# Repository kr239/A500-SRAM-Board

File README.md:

# A500-SRAM-Board

As with the previous DRAM board project, this will allow you to replace the old 44256 DRAM chips on your A500 with newer SRAM memory - a single 8Mbit chip, in fact. 

It's a lot simpler design, as there's just the single SRAM chip, a single 74ABT00 Quad NAND and a 74ABT821 10-bit D-Type Flip-Flop multiplexing the address lines.

The SRAM chip is a CY62157ESL-45ZSXI available from Mouser for less than £9 (at time of writing).

Ignore the image of the sockets, it's what KiCad generates as the 3D model.

Project is all done in KiCad 5.1.2

# Bill of Materials

4 x X7R 0.1uF MLCC SMD Capacitors (1206 (imperial)) - https://www.mouser.co.uk/ProductDetail/KEMET/C1206C104K4RACAUTO?qs=ds50AKTGxA8wfdh9NdUErA%3D%3D

1 x CY62157ESL-45ZSXI 8Mbit (512K x 16) SRAM (Cypress) - https://www.mouser.co.uk/ProductDetail/Cypress-Semiconductor/CY62157ESL-45ZSXI?qs=sGAEpiMZZMt9mBA6nIyysFkPZ0BxsYL2O8lsqoQk61s%3D

1 x SN74ABT821ADWR (SOIC-24) 10-bit D-Type Flip Flop (Texas Instruments) - https://www.mouser.co.uk/ProductDetail/Texas-Instruments/SN74ABT821ADWR?qs=FM6NhYOeeBXxX%2Fnpl0SzFQ%3D%3D

1 x 74ABT00D-T Quad Input NAND Gate (Nexperia) - https://www.mouser.co.uk/ProductDetail/Nexperia/74ABT00D118?qs=sGAEpiMZZMtMa9lbYwD6ZKUVY3zpSJbelxTPifZhJv0%3D

16 x 10-pin SIL Headers (Harwin M20-9991046) - https://www.mouser.co.uk/ProductDetail/Harwin/M20-9991046?qs=%2Fha2pyFaduidlkUepihCFfAt%252B%2FaLAftwmcRSbK8wUk3YgWpZFdsPYA%3D%3D

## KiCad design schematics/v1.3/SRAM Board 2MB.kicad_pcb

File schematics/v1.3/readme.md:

This is a significantly revised design based around two SRAM chips, using the buffered A9 input from U34 to provide sufficient address lines. This board will give 2MB CHIP RAM in an A500+ & the trapdoor expansion will be rendered useless for any memory expansions.

This board also has seen the design optimized significantly for low z-height, meaning it shouldn't foul the keyboard in a stock A500+ case. 

v1.3 also sees the introduction of an additional D-Type, Positive Edge triggered flip flop to feed A18 on the SRAM, rather than relying on /BRAS0 alone.

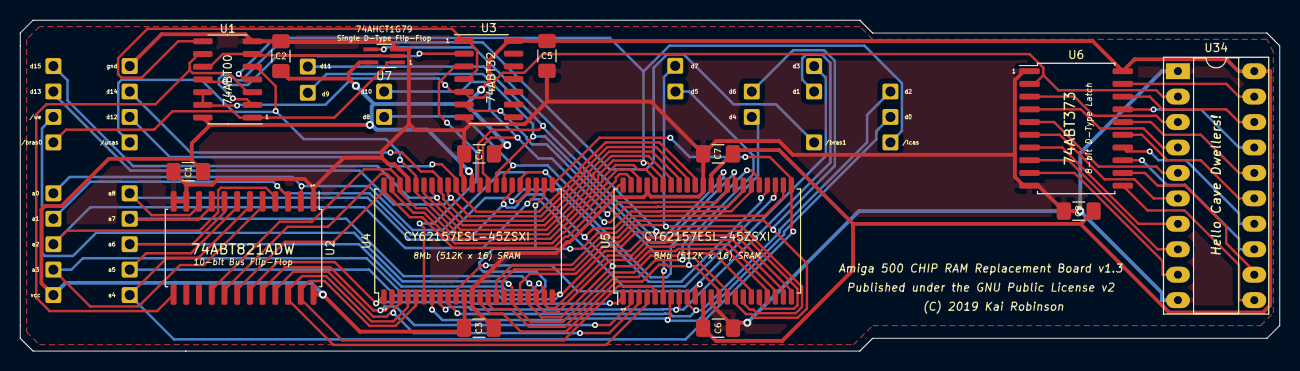
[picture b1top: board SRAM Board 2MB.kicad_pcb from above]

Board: 2 copper layers, 125.7 x 33.0 mm, 48 parts (0 on the bottom side), 64 nets.

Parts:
C1, C2, C3, C4, C5, C6, C7, C8: 0.1uF; C_1206_3216Metric_Pad1.42x1.75mm_HandSolder
J1, J2, J3, J4, J5, J6, J7, J8, J9, J10, J11, J12, J13, J14, J15, J16, J17, J18, J19, J20, J21, J22, J23, J24, J25, J26, J27, J28, J29, J30, J31, J32: Conn_01x01; PinHeader_1x01_P2.54mm_Vertical
U1: 74ABT00; SOIC-14_3.9x8.7mm_P1.27mm
U2: 74ABT821ADW; SOIC-24W_7.5x15.4mm_P1.27mm
U3: 74ABT32; SOIC-14_3.9x8.7mm_P1.27mm
U4, U5: CY62157ESL-45ZSXI; TSOP-II-44_10.16x18.41mm_P0.8mm_copy
U6: 74ABT373; SOIC-20W_7.5x12.8mm_P1.27mm
U7: 74AHCT1G79; SOT-353_SC-70-5_Handsoldering
U34: 74LS373; DIP-20_W7.62mm_Socket_LongPads

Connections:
/1d: U6.3, U34.3
/2d: U6.4, U34.4
/2q: U6.5, U34.5
/3d: U6.7, U34.7
/3q: U6.6, U34.6
/4d: U6.8, U34.8
/4q: U6.9, U34.9
/5d: U6.13, U34.13
/5q: U6.12, U34.12
/6d: U6.14, U34.14
/6q: U6.15, U34.15
/7d: U6.17, U34.17
/7q: U6.16, U34.16
/8d: U6.18, U34.18
/8q: U6.19, U34.19
/_bras0: J17.1, U1.1, U7.1
/_bras1: J18.1, U1.2
/_cas: U1.6, U1.10, U7.2
/_ceu4: U3.3, U4.6
/_ceu5: U3.6, U5.6
/_invbdra9: U1.11, U3.2
/_lcas: J22.1, U1.4, U4.39, U5.39
/_sramce: U1.8, U3.1, U3.4
/_ucas: J21.1, U1.5, U4.40, U5.40
/_we: J23.1, U4.17, U5.17
/a0: J24.1, U2.2, U4.27, U5.27
/a1: J25.1, U2.3, U4.26, U5.26
/a2: J26.1, U2.4, U4.25, U5.25
/a3: J27.1, U2.5, U4.24, U5.24
/a4: J28.1, U2.6, U4.23, U5.23
/a5: J29.1, U2.7, U4.22, U5.22
/a6: J30.1, U2.8, U4.21, U5.21
/a7: J31.1, U2.9, U4.20, U5.20
/a8: J32.1, U2.10, U4.19, U4.28, U5.19, U5.28
/a18: U4.18, U5.18, U7.4
/bdra9: U1.12, U1.13, U3.5, U6.2, U34.2
/clk: U1.3, U1.9, U2.13
/d0: J1.1, U4.7, U5.7
/d1: J2.1, U4.8, U5.8
/d2: J3.1, U4.9, U5.9
/d3: J4.1, U4.10, U5.10
/d4: J5.1, U4.13, U5.13
/d5: J6.1, U4.14, U5.14
/d6: J7.1, U4.15, U5.15
/d7: J8.1, U4.16, U5.16
/d8: J9.1, U4.29, U5.29
/d9: J10.1, U4.30, U5.30
/d10: J11.1, U4.31, U5.31
/d11: J12.1, U4.32, U5.32
/d12: J13.1, U4.35, U5.35
/d13: J14.1, U4.36, U5.36
/d14: J15.1, U4.37, U5.37
/d15: J16.1, U4.38, U5.38
/ma0: U2.23, U4.5, U5.5
/ma1: U2.22, U4.4, U5.4
/ma2: U2.21, U4.3, U5.3
/ma3: U2.20, U4.2, U5.2
/ma4: U2.19, U4.1, U5.1
/ma5: U2.18, U4.44, U5.44
/ma6: U2.17, U4.43, U5.43
/ma7: U2.16, U4.42, U5.42
/u34_le: U6.11, U34.11
GND: C1.2, C2.2, C3.2, C4.2, C5.2, C6.2, C7.2, C8.2, J20.1, U1.7, U2.1, U2.11, U2.12, U3.7, U4.12, U4.34, U4.41, U5.12, U5.34, U5.41, U6.1, U6.10, U7.3, U34.1, U34.10
VCC: C1.1, C2.1, C3.1, C4.1, C5.1, C6.1, C7.1, C8.1, J19.1, U1.14, U2.24, U3.14, U4.11, U4.33, U5.11, U5.33, U6.20, U7.5, U34.20

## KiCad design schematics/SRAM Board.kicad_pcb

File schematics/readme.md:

Remember to grab the A500 Parts Library so that you have the correct footprints.

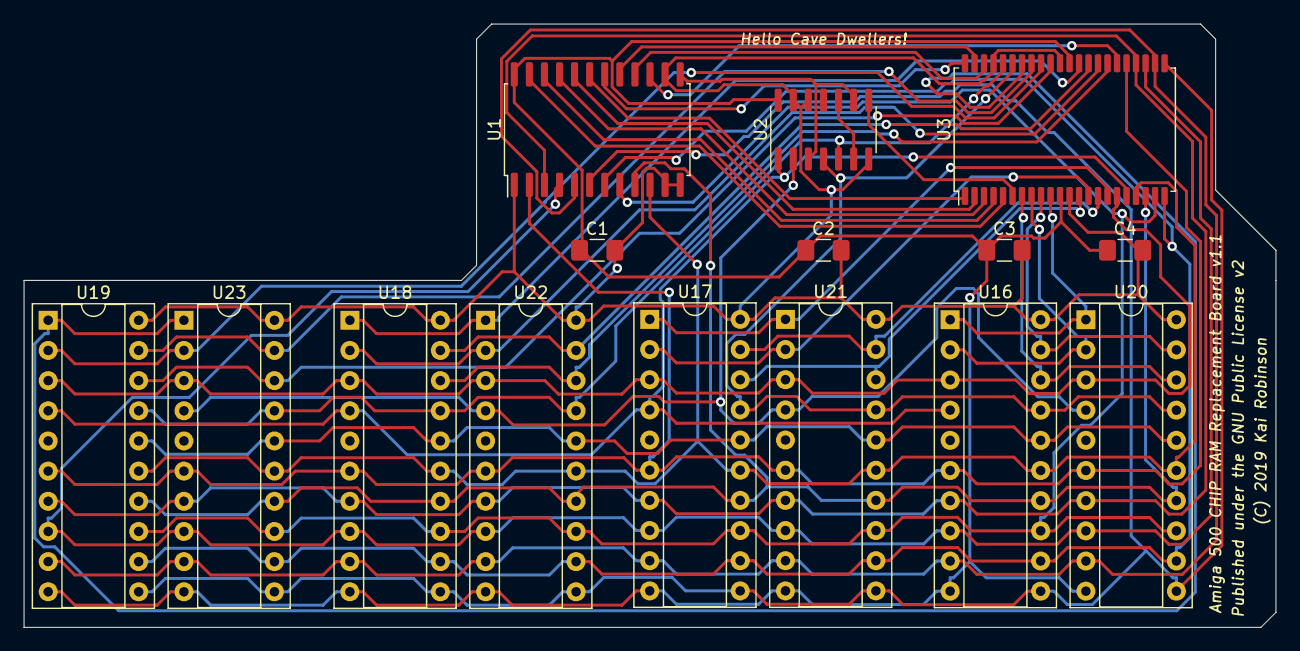
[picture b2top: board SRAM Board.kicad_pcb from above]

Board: 2 copper layers, 105.4 x 50.8 mm, 15 parts (0 on the bottom side), 45 nets.

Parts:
C1, C2, C3, C4: 0.1uF; C_1206_3216Metric_Pad1.42x1.75mm_HandSolder
U1: SN74ABT821ADW; SOIC-24W_7.5x15.4mm_P1.27mm
U2: 74HC00; SOIC-14_3.9x8.7mm_P1.27mm
U3: CY62157ESL-45ZSXI; TSOP-II-44_10.16x18.41mm_P0.8mm_copy
U16, U17, U18, U19, U20, U21, U22, U23: 44256_DRAM; DIP-20_W7.62mm_Socket

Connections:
/_bras0: U2.1, U3.18, U16.4, U17.4, U18.4, U19.4
/_bras1: U2.2, U20.4, U21.4, U22.4, U23.4
/_cas: U2.6, U2.10
/_lcas: U2.4, U3.39, U16.17, U17.17, U20.17, U21.17
/_oe: U16.16, U17.16, U18.16, U19.16, U20.16, U21.16, U22.16, U23.16
/_sramce: U2.8, U3.6
/_ucas: U2.5, U3.40, U18.17, U19.17, U22.17, U23.17
/_we: U3.17, U16.3, U17.3, U18.3, U19.3, U20.3, U21.3, U22.3, U23.3
/a0: U1.2, U3.27, U16.6, U17.6, U18.6, U19.6, U20.6, U21.6, U22.6, U23.6
/a1: U1.3, U3.26, U16.7, U17.7, U18.7, U19.7, U20.7, U21.7, U22.7, U23.7
/a2: U1.4, U3.25, U16.8, U17.8, U18.8, U19.8, U20.8, U21.8, U22.8, U23.8
/a3: U1.5, U3.24, U16.9, U17.9, U18.9, U19.9, U20.9, U21.9, U22.9, U23.9
/a4: U1.6, U3.23, U16.11, U17.11, U18.11, U19.11, U20.11, U21.11, U22.11, U23.11
/a5: U1.7, U3.22, U16.12, U17.12, U18.12, U19.12, U20.12, U21.12, U22.12, U23.12
/a6: U1.8, U3.21, U16.13, U17.13, U18.13, U19.13, U20.13, U21.13, U22.13, U23.13
/a7: U1.9, U3.20, U16.14, U17.14, U18.14, U19.14, U20.14, U21.14, U22.14, U23.14
/a8: U1.10, U3.19, U16.15, U17.15, U18.15, U19.15, U20.15, U21.15, U22.15, U23.15
/clk: U1.13, U2.3, U2.9
/d0: U3.7, U16.18, U20.18
/d1: U3.8, U16.2, U20.2
/d2: U3.9, U16.19, U20.19
/d3: U3.10, U16.1, U20.1
/d4: U3.13, U17.18, U21.18
/d5: U3.14, U17.2, U21.2
/d6: U3.15, U17.19, U21.19
/d7: U3.16, U17.1, U21.1
/d8: U3.29, U18.18, U22.18
/d9: U3.30, U18.2, U22.2
/d10: U3.31, U18.19, U22.19
/d11: U3.32, U18.1, U22.1
/d12: U3.35, U19.18, U23.18
/d13: U3.36, U19.2, U23.2
/d14: U3.37, U19.19, U23.19
/d15: U3.38, U19.1, U23.1
/gnd: C1.2, C2.2, C3.2, C4.2, U1.1, U1.11, U1.12, U1.14, U2.7, U2.12, U2.13, U3.12, U3.34, U3.41, U16.20, U17.20, U18.20, U19.20, U20.20, U21.20, U22.20, U23.20
/ma0: U1.23, U3.5
/ma1: U1.22, U3.4
/ma2: U1.21, U3.3
/ma3: U1.20, U3.2
/ma4: U1.19, U3.1
/ma5: U1.18, U3.44
/ma6: U1.17, U3.43
/ma7: U1.16, U3.42
/ma8: U1.15, U3.28
/vcc5: C1.1, C2.1, C3.1, C4.1, U1.24, U2.14, U3.11, U3.33, U16.10, U17.10, U18.10, U19.10, U20.10, U21.10, U22.10, U23.10

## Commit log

2019-05-16 Create LICENSE
2019-05-17 Add files via upload
    Fixing a glaring error - I had grounded A18, rather than assigning it to _bras0 instead.
2019-05-17 Add files via upload
    Re-done due to A18 being grounded rather than being assigned to _bras0.
2019-05-18 Add files via upload
    Switching the 74ABT00 pin 11 from GND to NC
2019-05-19 Add files via upload
    Bottom Solder Mask had been excluded in error
2019-05-19 Update README.md
    Updated SIL Header for Mouser availability
2019-05-20 Add files via upload
    Actually remembered the rear mask :D
2019-06-06 Changed back to 2 layer board
    Changed to 2 layer board, using thicker power traces and a copper fill on both sides for VCC and GND planes.
2019-06-06 Create SRAM Board 2MB Orth1.png
    Updated PNG
2019-06-09 Removing extraneous directory.
2019-06-09 New Board Layout
2019-06-09 Updating images
2019-10-09 Add mouser links to BOM
2019-10-09 Correct package size description for flip-flop

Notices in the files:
schematics/SRAM Board.kicad_pcb:
(C) 2019 Kai Robinson
Published under the GNU Public License v2
